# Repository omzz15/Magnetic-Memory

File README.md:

*Note: Any time I say MAD, I am refering to the memory address.

# Overview

Magnetic-core memory was an early form of non-volatile random access memory (RAM) used in early computing, notably the Apollo Guidance Computers. I am working with a friend to create our own magnetic core memory to interface with an 8-bit computer. This repository contains the code, schematics, and PCBs we make. Currently, we have made the schematic and PCB for the logic component of the memory as well as code to emulate the rest of the memory and interface with computers through serial. This is still a work in progress and has a long way to go but I thought I would share what I have.

TODO write updated docs

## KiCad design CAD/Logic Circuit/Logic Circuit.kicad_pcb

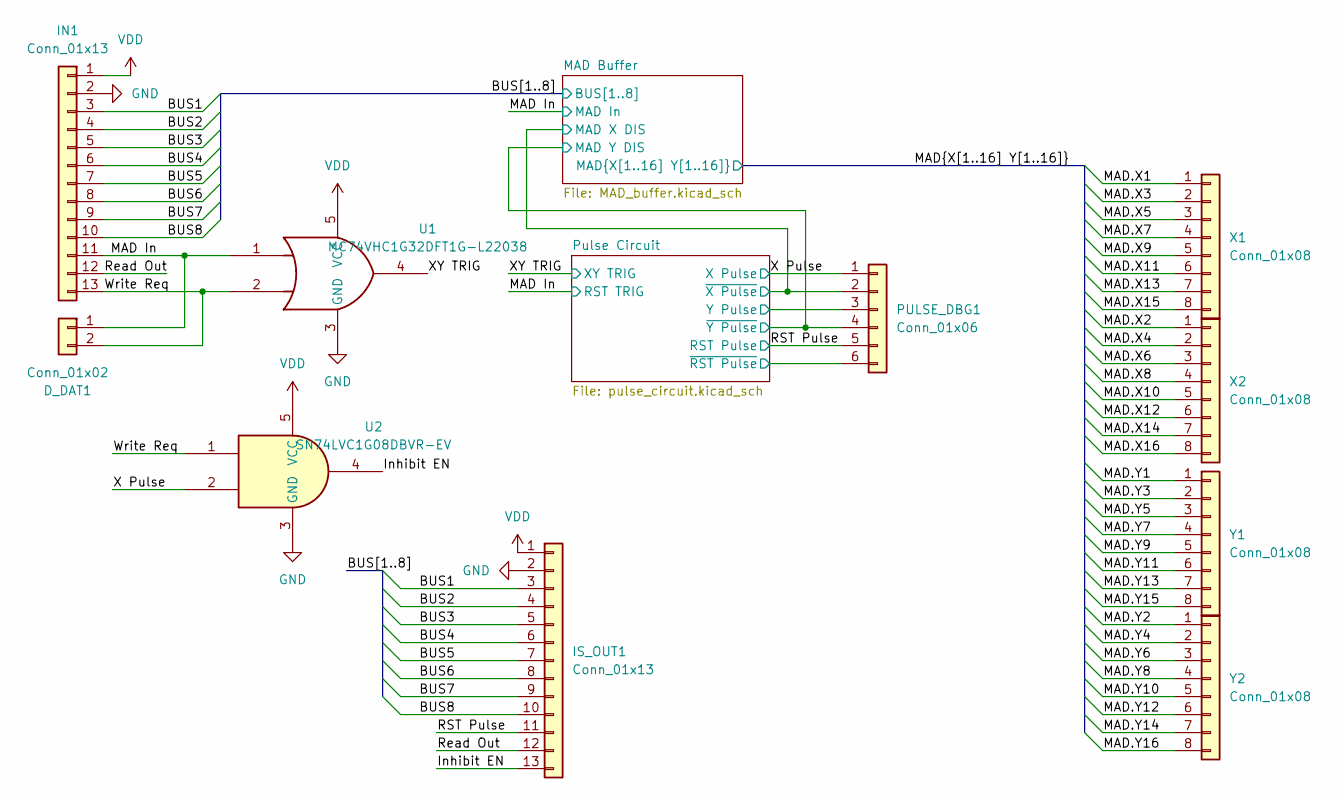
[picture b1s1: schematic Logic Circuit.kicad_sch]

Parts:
D_DAT1: Conn_01x02; PinSocket_1x02_P2.54mm_Vertical
IN1: Conn_01x13; PinHeader_1x13_P2.54mm_Vertical
IS_OUT1: Conn_01x13; PinHeader_1x13_P2.54mm_Vertical
PULSE_DBG1: Conn_01x06; PinSocket_1x06_P2.54mm_Vertical
U1: MC74VHC1G32DFT1G-L22038; SOT-353_SC-70-5_Handsoldering
U2: SN74LVC1G08DBVR-EV; SOT-23-5_HandSoldering
X1, X2: Conn_01x08; PinHeader_1x08_P2.54mm_Vertical
Y1, Y2: Conn_01x08; PinHeader_1x08_P2.54mm_Vertical

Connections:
/BUS1: IN1.3, IS_OUT1.3; also elsewhere on the board
/BUS2: IN1.4, IS_OUT1.4; also elsewhere on the board
/BUS3: IN1.5, IS_OUT1.5; also elsewhere on the board
/BUS4: IN1.6, IS_OUT1.6; also elsewhere on the board
/BUS5: IN1.7, IS_OUT1.7; also elsewhere on the board
/BUS6: IN1.8, IS_OUT1.8; also elsewhere on the board
/BUS7: IN1.9, IS_OUT1.9; also elsewhere on the board
/BUS8: IN1.10, IS_OUT1.10; also elsewhere on the board
/Inhibit EN: IS_OUT1.13, U2.4
/MAD Buffer/MAD X DIS: PULSE_DBG1.2; also elsewhere on the board
/MAD Buffer/MAD Y DIS: PULSE_DBG1.4; also elsewhere on the board
/MAD In: D_DAT1.1, IN1.11, U1.1; also elsewhere on the board
/MAD.X1: X1.1; also elsewhere on the board
/MAD.X2: X2.1; also elsewhere on the board
/MAD.X3: X1.2; also elsewhere on the board
/MAD.X4: X2.2; also elsewhere on the board
/MAD.X5: X1.3; also elsewhere on the board
/MAD.X6: X2.3; also elsewhere on the board
/MAD.X7: X1.4; also elsewhere on the board
/MAD.X8: X2.4; also elsewhere on the board
/MAD.X9: X1.5; also elsewhere on the board
/MAD.X10: X2.5; also elsewhere on the board
/MAD.X11: X1.6; also elsewhere on the board
/MAD.X12: X2.6; also elsewhere on the board
/MAD.X13: X1.7; also elsewhere on the board
/MAD.X14: X2.7; also elsewhere on the board
/MAD.X15: X1.8; also elsewhere on the board
/MAD.X16: X2.8; also elsewhere on the board
/MAD.Y1: Y1.1; also elsewhere on the board
/MAD.Y2: Y2.1; also elsewhere on the board
/MAD.Y3: Y1.2; also elsewhere on the board
/MAD.Y4: Y2.2; also elsewhere on the board
/MAD.Y5: Y1.3; also elsewhere on the board
/MAD.Y6: Y2.3; also elsewhere on the board
/MAD.Y7: Y1.4; also elsewhere on the board
/MAD.Y8: Y2.4; also elsewhere on the board
/MAD.Y9: Y1.5; also elsewhere on the board
/MAD.Y10: Y2.5; also elsewhere on the board
/MAD.Y11: Y1.6; also elsewhere on the board
/MAD.Y12: Y2.6; also elsewhere on the board
/MAD.Y13: Y1.7; also elsewhere on the board
/MAD.Y14: Y2.7; also elsewhere on the board
/MAD.Y15: Y1.8; also elsewhere on the board
/MAD.Y16: Y2.8; also elsewhere on the board
/Pulse Circuit/Y Pulse: PULSE_DBG1.3; also elsewhere on the board
/Pulse Circuit/~RST Pulse: PULSE_DBG1.6; also elsewhere on the board
/RST Pulse: IS_OUT1.11, PULSE_DBG1.5; also elsewhere on the board
/Read Out: IN1.12, IS_OUT1.12
/Write Req: D_DAT1.2, IN1.13, U1.2, U2.1
/X Pulse: PULSE_DBG1.1, U2.2; also elsewhere on the board
/XY TRIG: U1.4; also elsewhere on the board
GND: IN1.2, IS_OUT1.2, U1.3 (GND), U2.3 (GND); also elsewhere on the board
VDD: IN1.1, IS_OUT1.1, U1.5 (VCC), U2.5 (VCC); also elsewhere on the board

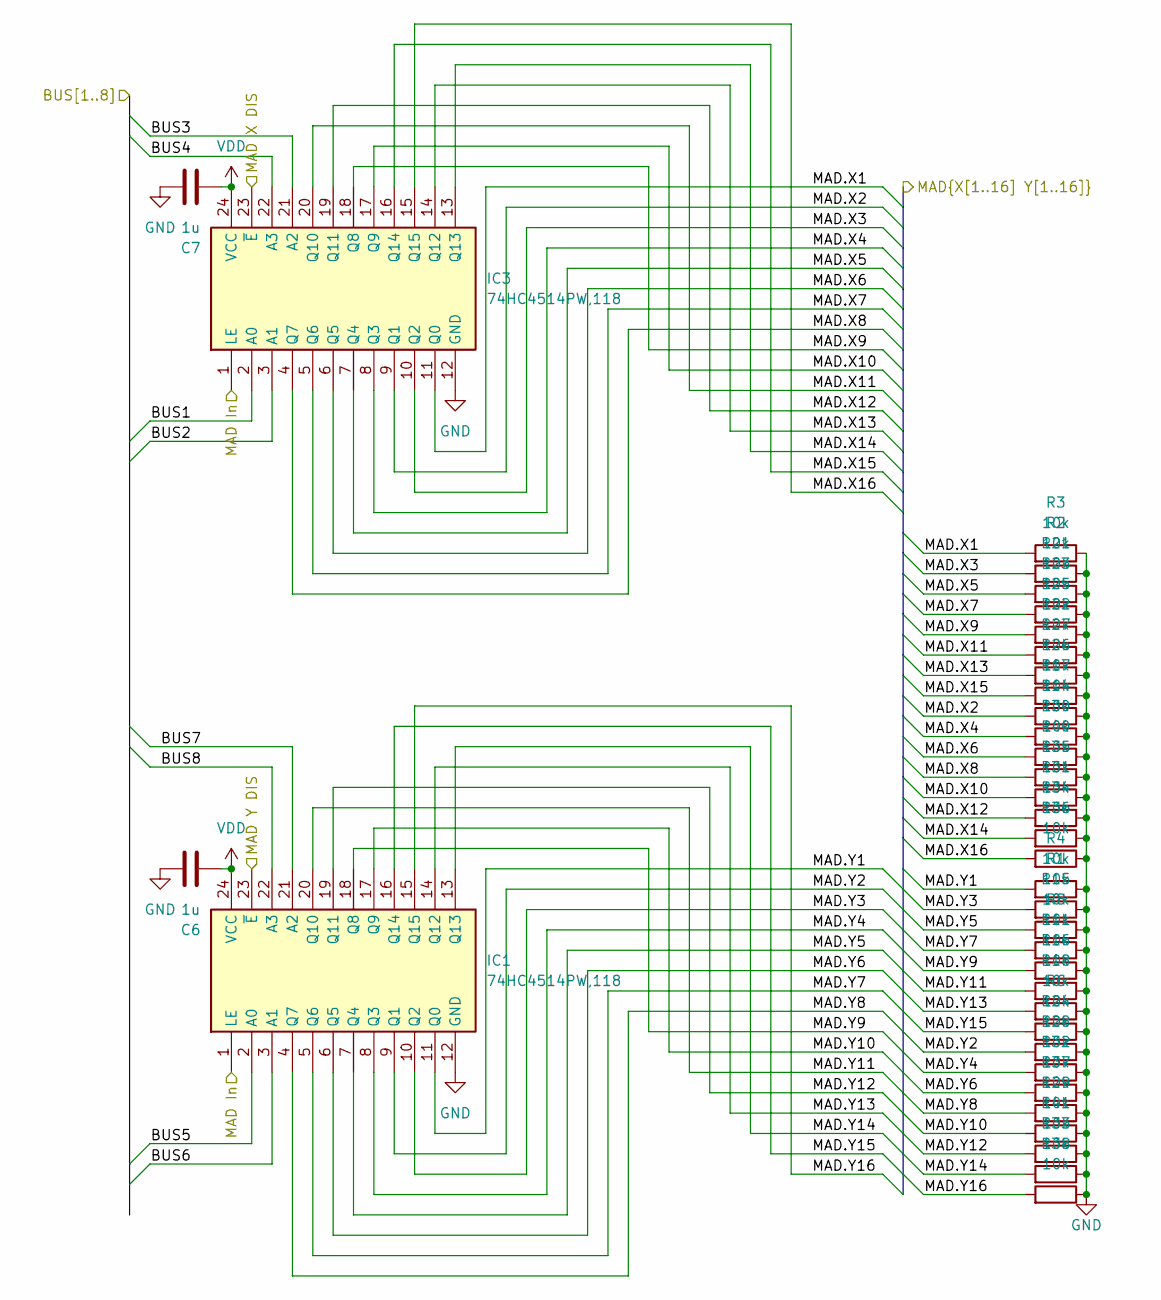
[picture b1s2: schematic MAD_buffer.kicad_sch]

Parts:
C6, C7: 1u; C_0603_1608Metric_Pad1.08x0.95mm_HandSolder
IC1, IC3: 74HC4514PW,118; SOP65P640X110-24N; Mouser Part Number 771-HC4514PW118
R1, R2, R3, R4, R6, R8, R11, R14, R15, R16, R17, R18, R21, R22, R23, R24, R25, R26, R27, R28, R29, R30, R31, R32, R33, R34, R35, R36, R37, R38, R40, R41: 10k; R_0603_1608Metric_Pad0.98x0.95mm_HandSolder

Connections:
/BUS1: IC3.2 (A0); also elsewhere on the board
/BUS2: IC3.3 (A1); also elsewhere on the board
/BUS3: IC3.21 (A2); also elsewhere on the board
/BUS4: IC3.22 (A3); also elsewhere on the board
/BUS5: IC1.2 (A0); also elsewhere on the board
/BUS6: IC1.3 (A1); also elsewhere on the board
/BUS7: IC1.21 (A2); also elsewhere on the board
/BUS8: IC1.22 (A3); also elsewhere on the board
/MAD Buffer/MAD X DIS: IC3.23 (~E); also elsewhere on the board
/MAD Buffer/MAD Y DIS: IC1.23 (~E); also elsewhere on the board
/MAD In: IC1.1 (LE), IC3.1 (LE); also elsewhere on the board
/MAD.X1: IC3.11 (Q0), R3.2; also elsewhere on the board
/MAD.X2: IC3.9 (Q1), R17.2; also elsewhere on the board
/MAD.X3: IC3.10 (Q2), R2.2; also elsewhere on the board
/MAD.X4: IC3.8 (Q3), R14.2; also elsewhere on the board
/MAD.X5: IC3.7 (Q4), R21.2; also elsewhere on the board
/MAD.X6: IC3.6 (Q5), R30.2; also elsewhere on the board
/MAD.X7: IC3.5 (Q6), R23.2; also elsewhere on the board
/MAD.X8: IC3.4 (Q7), R40.2; also elsewhere on the board
/MAD.X9: IC3.18 (Q8), R25.2; also elsewhere on the board
/MAD.X10: IC3.17 (Q9), R35.2; also elsewhere on the board
/MAD.X11: IC3.20 (Q10), R22.2; also elsewhere on the board
/MAD.X12: IC3.19 (Q11), R31.2; also elsewhere on the board
/MAD.X13: IC3.14 (Q12), R27.2; also elsewhere on the board
/MAD.X14: IC3.13 (Q13), R34.2; also elsewhere on the board
/MAD.X15: IC3.16 (Q14), R26.2; also elsewhere on the board
/MAD.X16: IC3.15 (Q15), R36.2; also elsewhere on the board
/MAD.Y1: IC1.11 (Q0), R4.2; also elsewhere on the board
/MAD.Y2: IC1.9 (Q1), R24.2; also elsewhere on the board
/MAD.Y3: IC1.10 (Q2), R1.2; also elsewhere on the board
/MAD.Y4: IC1.8 (Q3), R28.2; also elsewhere on the board
/MAD.Y5: IC1.7 (Q4), R15.2; also elsewhere on the board
/MAD.Y6: IC1.6 (Q5), R32.2; also elsewhere on the board
/MAD.Y7: IC1.5 (Q6), R8.2; also elsewhere on the board
/MAD.Y8: IC1.4 (Q7), R37.2; also elsewhere on the board
/MAD.Y9: IC1.18 (Q8), R11.2; also elsewhere on the board
/MAD.Y10: IC1.17 (Q9), R29.2; also elsewhere on the board
/MAD.Y11: IC1.20 (Q10), R16.2; also elsewhere on the board
/MAD.Y12: IC1.19 (Q11), R41.2; also elsewhere on the board
/MAD.Y13: IC1.14 (Q12), R18.2; also elsewhere on the board
/MAD.Y14: IC1.13 (Q13), R33.2; also elsewhere on the board
/MAD.Y15: IC1.16 (Q14), R6.2; also elsewhere on the board
/MAD.Y16: IC1.15 (Q15), R38.2; also elsewhere on the board
GND: C6.1, C7.1, IC1.12 (GND), IC3.12 (GND), R1.1, R2.1, R3.1, R4.1, R6.1, R8.1, R11.1, R14.1, R15.1, R16.1, R17.1, R18.1, R21.1, R22.1, R23.1, R24.1, R25.1, R26.1, R27.1, R28.1, R29.1, R30.1, R31.1, R32.1, R33.1, R34.1, R35.1, R36.1, R37.1, R38.1, R40.1, R41.1; also elsewhere on the board
VDD: C6.2, C7.2, IC1.24 (VCC), IC3.24 (VCC); also elsewhere on the board

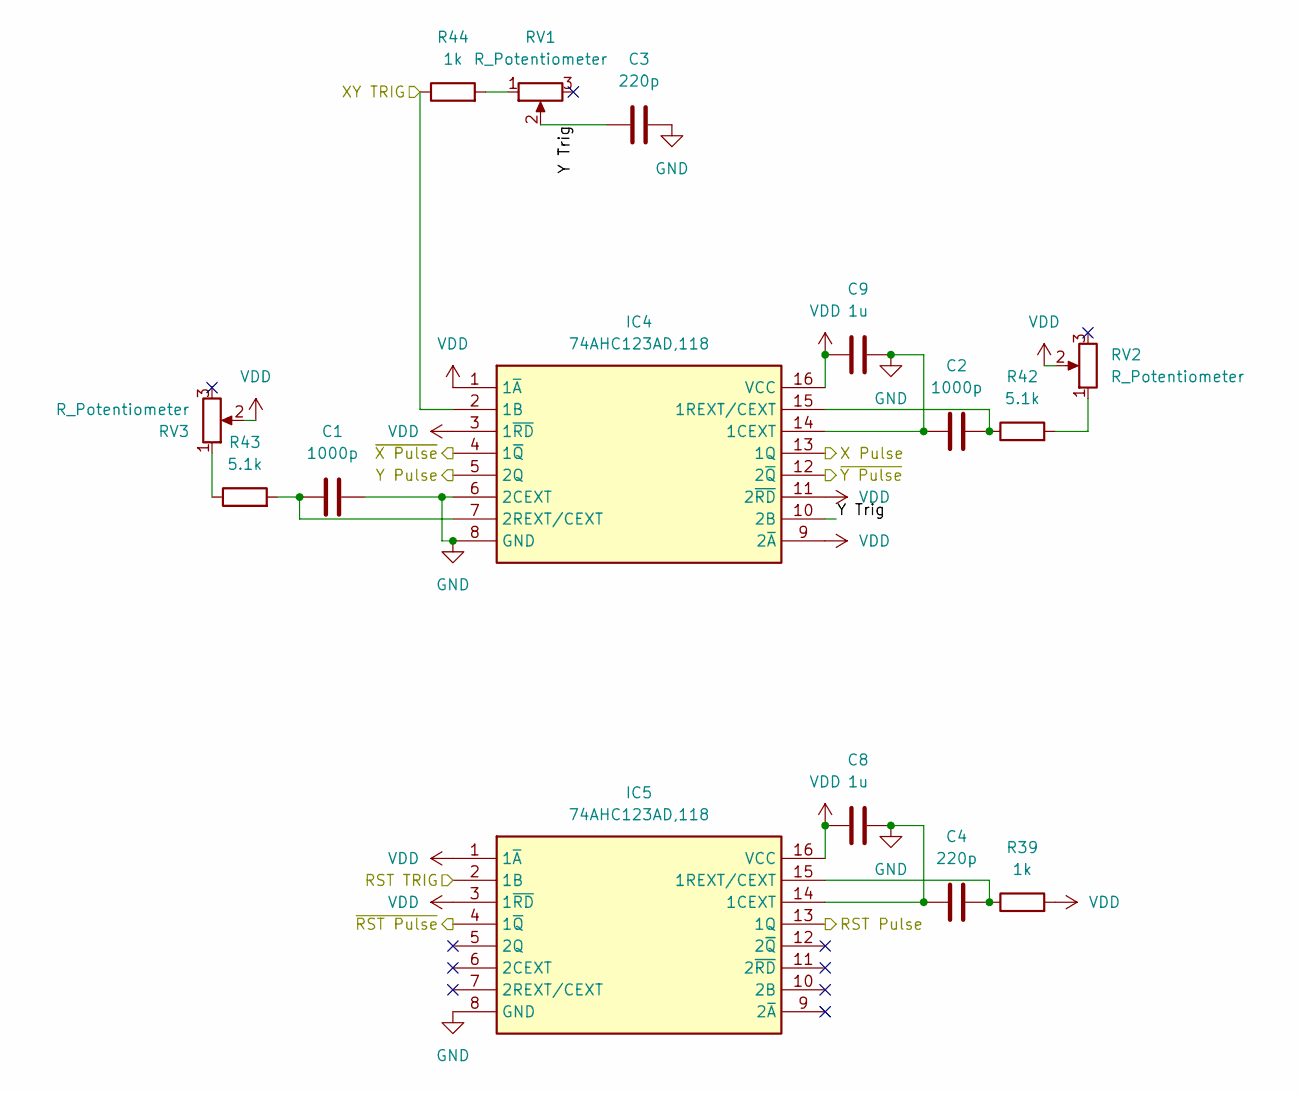
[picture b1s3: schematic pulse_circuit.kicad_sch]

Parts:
C1, C2: 1000p; C_0603_1608Metric_Pad1.08x0.95mm_HandSolder
C3, C4: 220p; C_0603_1608Metric_Pad1.08x0.95mm_HandSolder
C8, C9: 1u; C_0603_1608Metric_Pad1.08x0.95mm_HandSolder
IC4, IC5: 74AHC123AD,118; SOIC127P600X175-16N; Mouser Part Number 771-AHC123AD118
R39, R44: 1k; R_0603_1608Metric_Pad0.98x0.95mm_HandSolder
R42, R43: 5.1k; R_0603_1608Metric_Pad0.98x0.95mm_HandSolder
RV1, RV2, RV3: R_Potentiometer; Potentiometer_Bourns_3296W_Vertical

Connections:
/MAD Buffer/MAD X DIS: IC4.4 (1~Q); also elsewhere on the board
/MAD Buffer/MAD Y DIS: IC4.12 (2~Q); also elsewhere on the board
/MAD In: IC5.2 (1B); also elsewhere on the board
/Pulse Circuit/Y Pulse: IC4.5 (2Q); also elsewhere on the board
/Pulse Circuit/Y Trig: C3.1, IC4.10 (2B), RV1.2
/Pulse Circuit/~RST Pulse: IC5.4 (1~Q); also elsewhere on the board
/RST Pulse: IC5.13 (1Q); also elsewhere on the board
/X Pulse: IC4.13 (1Q); also elsewhere on the board
/XY TRIG: IC4.2 (1B), R44.1; also elsewhere on the board
GND: C1.2, C2.1, C3.2, C4.1, C8.1, C9.1, IC4.6 (2CEXT), IC4.8 (GND), IC4.14 (1CEXT), IC5.8 (GND), IC5.14 (1CEXT); also elsewhere on the board
unnamed: C2.2, IC4.15 (1REXT/CEXT), R42.1
unnamed: C1.1, IC4.7 (2REXT/CEXT), R43.2
unnamed: C4.2, IC5.15 (1REXT/CEXT), R39.1
unnamed: R42.2, RV2.1
unnamed: R43.1, RV3.1
unnamed: R44.2, RV1.1
VDD: C8.2, C9.2, IC4.1 (1~A), IC4.3 (1~RD), IC4.9 (2~A), IC4.11 (2~RD), IC4.16 (VCC), IC5.1 (1~A), IC5.3 (1~RD), IC5.16 (VCC), R39.2, RV2.2, RV3.2; also elsewhere on the board

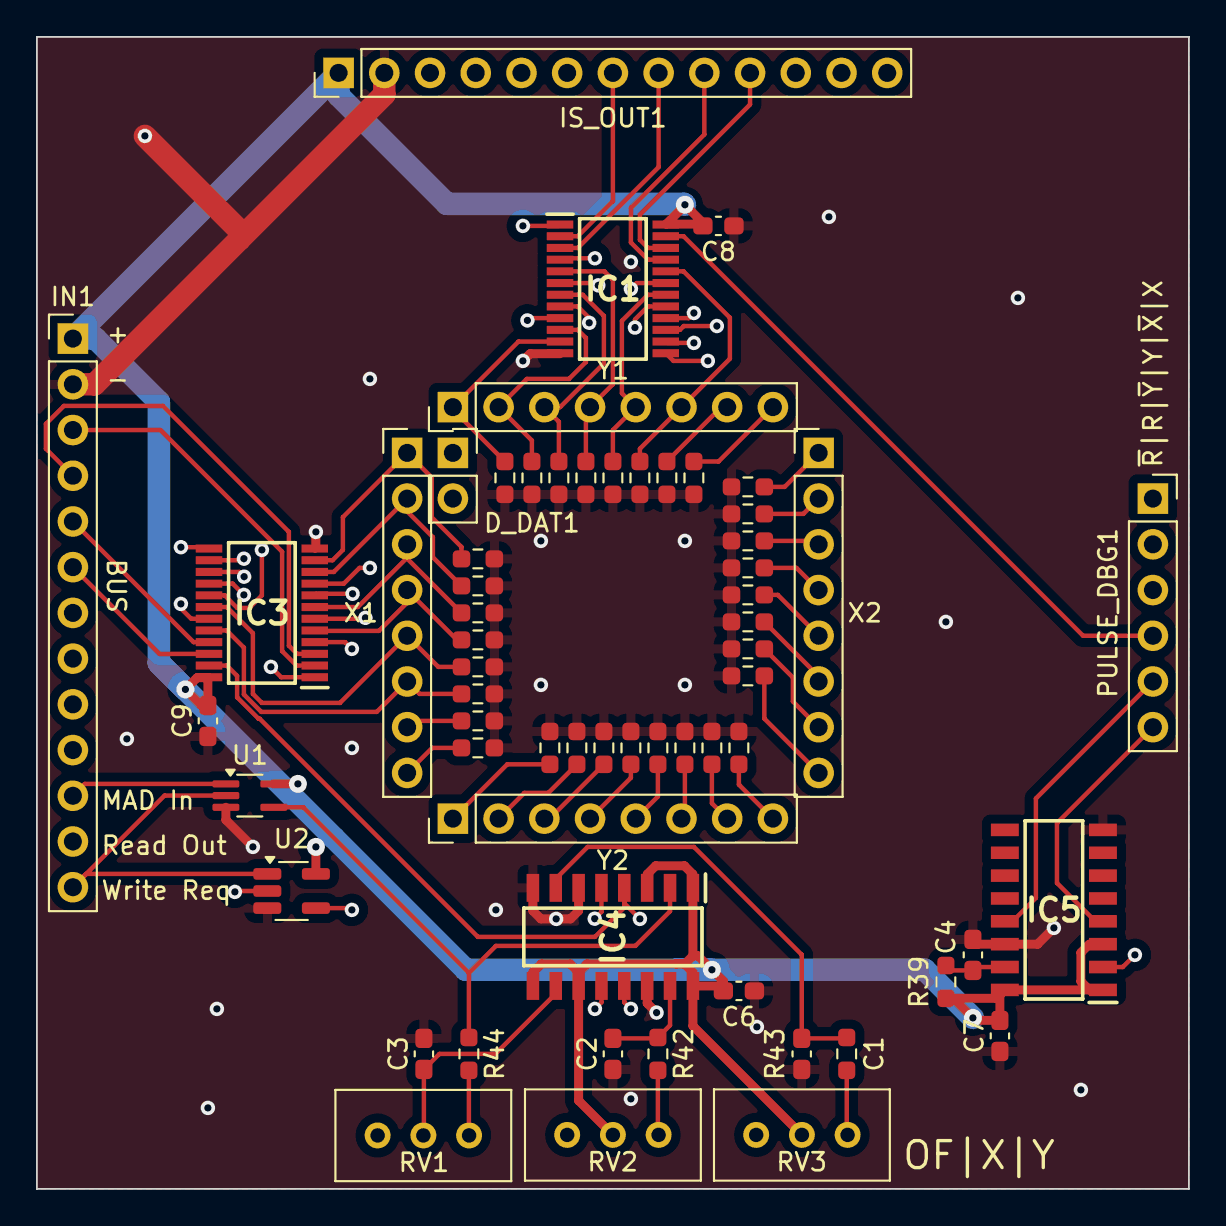
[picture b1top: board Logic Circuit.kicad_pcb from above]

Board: 4 copper layers, 64.0 x 64.0 mm, 61 parts (0 on the bottom side), 60 nets.

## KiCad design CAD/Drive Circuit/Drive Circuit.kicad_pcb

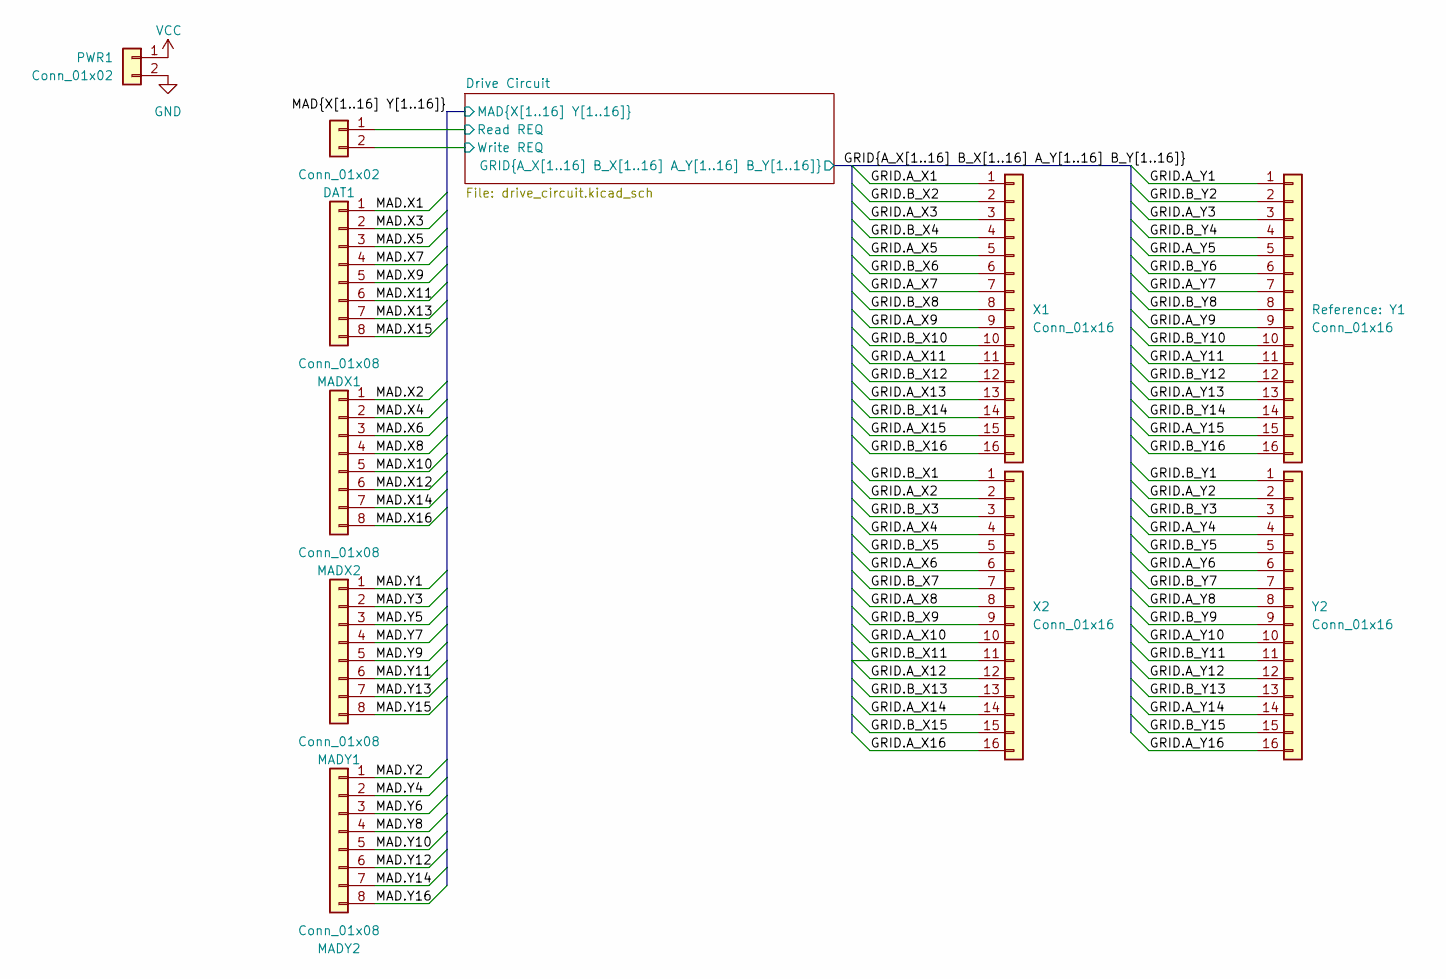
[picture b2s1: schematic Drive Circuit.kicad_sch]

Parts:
DAT1: Conn_01x02; PinHeader_1x02_P2.54mm_Vertical
MADX1, MADX2: Conn_01x08; PinHeader_1x08_P2.54mm_Vertical
MADY1, MADY2: Conn_01x08; PinHeader_1x08_P2.54mm_Vertical
PWR1: Conn_01x02; PinHeader_1x02_P2.54mm_Vertical
X1, X2: Conn_01x16; PinHeader_1x16_P2.54mm_Vertical
Y1, Y2: Conn_01x16; PinHeader_1x16_P2.54mm_Vertical

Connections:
/Drive Circuit/Read REQ: DAT1.1; also elsewhere on the board
/Drive Circuit/Write REQ: DAT1.2; also elsewhere on the board
/GRID.A_X1: X1.1; also elsewhere on the board
/GRID.A_X2: X2.2; also elsewhere on the board
/GRID.A_X3: X1.3; also elsewhere on the board
/GRID.A_X4: X2.4; also elsewhere on the board
/GRID.A_X5: X1.5; also elsewhere on the board
/GRID.A_X6: X2.6; also elsewhere on the board
/GRID.A_X7: X1.7; also elsewhere on the board
/GRID.A_X8: X2.8; also elsewhere on the board
/GRID.A_X9: X1.9; also elsewhere on the board
/GRID.A_X10: X2.10; also elsewhere on the board
/GRID.A_X11: X1.11; also elsewhere on the board
/GRID.A_X12: X2.12; also elsewhere on the board
/GRID.A_X13: X1.13; also elsewhere on the board
/GRID.A_X14: X2.14; also elsewhere on the board
/GRID.A_X15: X1.15; also elsewhere on the board
/GRID.A_X16: X2.16; also elsewhere on the board
/GRID.A_Y1: Y1.1; also elsewhere on the board
/GRID.A_Y2: Y2.2; also elsewhere on the board
/GRID.A_Y3: Y1.3; also elsewhere on the board
/GRID.A_Y4: Y2.4; also elsewhere on the board
/GRID.A_Y5: Y1.5; also elsewhere on the board
/GRID.A_Y6: Y2.6; also elsewhere on the board
/GRID.A_Y7: Y1.7; also elsewhere on the board
/GRID.A_Y8: Y2.8; also elsewhere on the board
/GRID.A_Y9: Y1.9; also elsewhere on the board
/GRID.A_Y10: Y2.10; also elsewhere on the board
/GRID.A_Y11: Y1.11; also elsewhere on the board
/GRID.A_Y12: Y2.12; also elsewhere on the board
/GRID.A_Y13: Y1.13; also elsewhere on the board
/GRID.A_Y14: Y2.14; also elsewhere on the board
/GRID.A_Y15: Y1.15; also elsewhere on the board
/GRID.A_Y16: Y2.16; also elsewhere on the board
/GRID.B_X1: X2.1; also elsewhere on the board
/GRID.B_X2: X1.2; also elsewhere on the board
/GRID.B_X3: X2.3; also elsewhere on the board
/GRID.B_X4: X1.4; also elsewhere on the board
/GRID.B_X5: X2.5; also elsewhere on the board
/GRID.B_X6: X1.6; also elsewhere on the board
/GRID.B_X7: X2.7; also elsewhere on the board
/GRID.B_X8: X1.8; also elsewhere on the board
/GRID.B_X9: X2.9; also elsewhere on the board
/GRID.B_X10: X1.10; also elsewhere on the board
/GRID.B_X11: X2.11; also elsewhere on the board
/GRID.B_X12: X1.12; also elsewhere on the board
/GRID.B_X13: X2.13; also elsewhere on the board
/GRID.B_X14: X1.14; also elsewhere on the board
/GRID.B_X15: X2.15; also elsewhere on the board
/GRID.B_X16: X1.16; also elsewhere on the board
/GRID.B_Y1: Y2.1; also elsewhere on the board
/GRID.B_Y2: Y1.2; also elsewhere on the board
/GRID.B_Y3: Y2.3; also elsewhere on the board
/GRID.B_Y4: Y1.4; also elsewhere on the board
/GRID.B_Y5: Y2.5; also elsewhere on the board
/GRID.B_Y6: Y1.6; also elsewhere on the board
/GRID.B_Y7: Y2.7; also elsewhere on the board
/GRID.B_Y8: Y1.8; also elsewhere on the board
/GRID.B_Y9: Y2.9; also elsewhere on the board
/GRID.B_Y10: Y1.10; also elsewhere on the board
/GRID.B_Y11: Y2.11; also elsewhere on the board
/GRID.B_Y12: Y1.12; also elsewhere on the board
/GRID.B_Y13: Y2.13; also elsewhere on the board
/GRID.B_Y14: Y1.14; also elsewhere on the board
/GRID.B_Y15: Y2.15; also elsewhere on the board
/GRID.B_Y16: Y1.16; also elsewhere on the board
/MAD.X1: MADX1.1; also elsewhere on the board
/MAD.X2: MADX2.1; also elsewhere on the board
/MAD.X3: MADX1.2; also elsewhere on the board
/MAD.X4: MADX2.2; also elsewhere on the board
/MAD.X5: MADX1.3; also elsewhere on the board
/MAD.X6: MADX2.3; also elsewhere on the board
/MAD.X7: MADX1.4; also elsewhere on the board
/MAD.X8: MADX2.4; also elsewhere on the board
/MAD.X9: MADX1.5; also elsewhere on the board
/MAD.X10: MADX2.5; also elsewhere on the board
/MAD.X11: MADX1.6; also elsewhere on the board
/MAD.X12: MADX2.6; also elsewhere on the board
/MAD.X13: MADX1.7; also elsewhere on the board
/MAD.X14: MADX2.7; also elsewhere on the board
/MAD.X15: MADX1.8; also elsewhere on the board
/MAD.X16: MADX2.8; also elsewhere on the board
/MAD.Y1: MADY1.1; also elsewhere on the board
/MAD.Y2: MADY2.1; also elsewhere on the board
/MAD.Y3: MADY1.2; also elsewhere on the board
/MAD.Y4: MADY2.2; also elsewhere on the board
/MAD.Y5: MADY1.3; also elsewhere on the board
/MAD.Y6: MADY2.3; also elsewhere on the board
/MAD.Y7: MADY1.4; also elsewhere on the board
/MAD.Y8: MADY2.4; also elsewhere on the board
/MAD.Y9: MADY1.5; also elsewhere on the board
/MAD.Y10: MADY2.5; also elsewhere on the board
/MAD.Y11: MADY1.6; also elsewhere on the board
/MAD.Y12: MADY2.6; also elsewhere on the board
/MAD.Y13: MADY1.7; also elsewhere on the board
/MAD.Y14: MADY2.7; also elsewhere on the board
/MAD.Y15: MADY1.8; also elsewhere on the board
/MAD.Y16: MADY2.8; also elsewhere on the board
GND: PWR1.2; also elsewhere on the board
VCC: PWR1.1; also elsewhere on the board

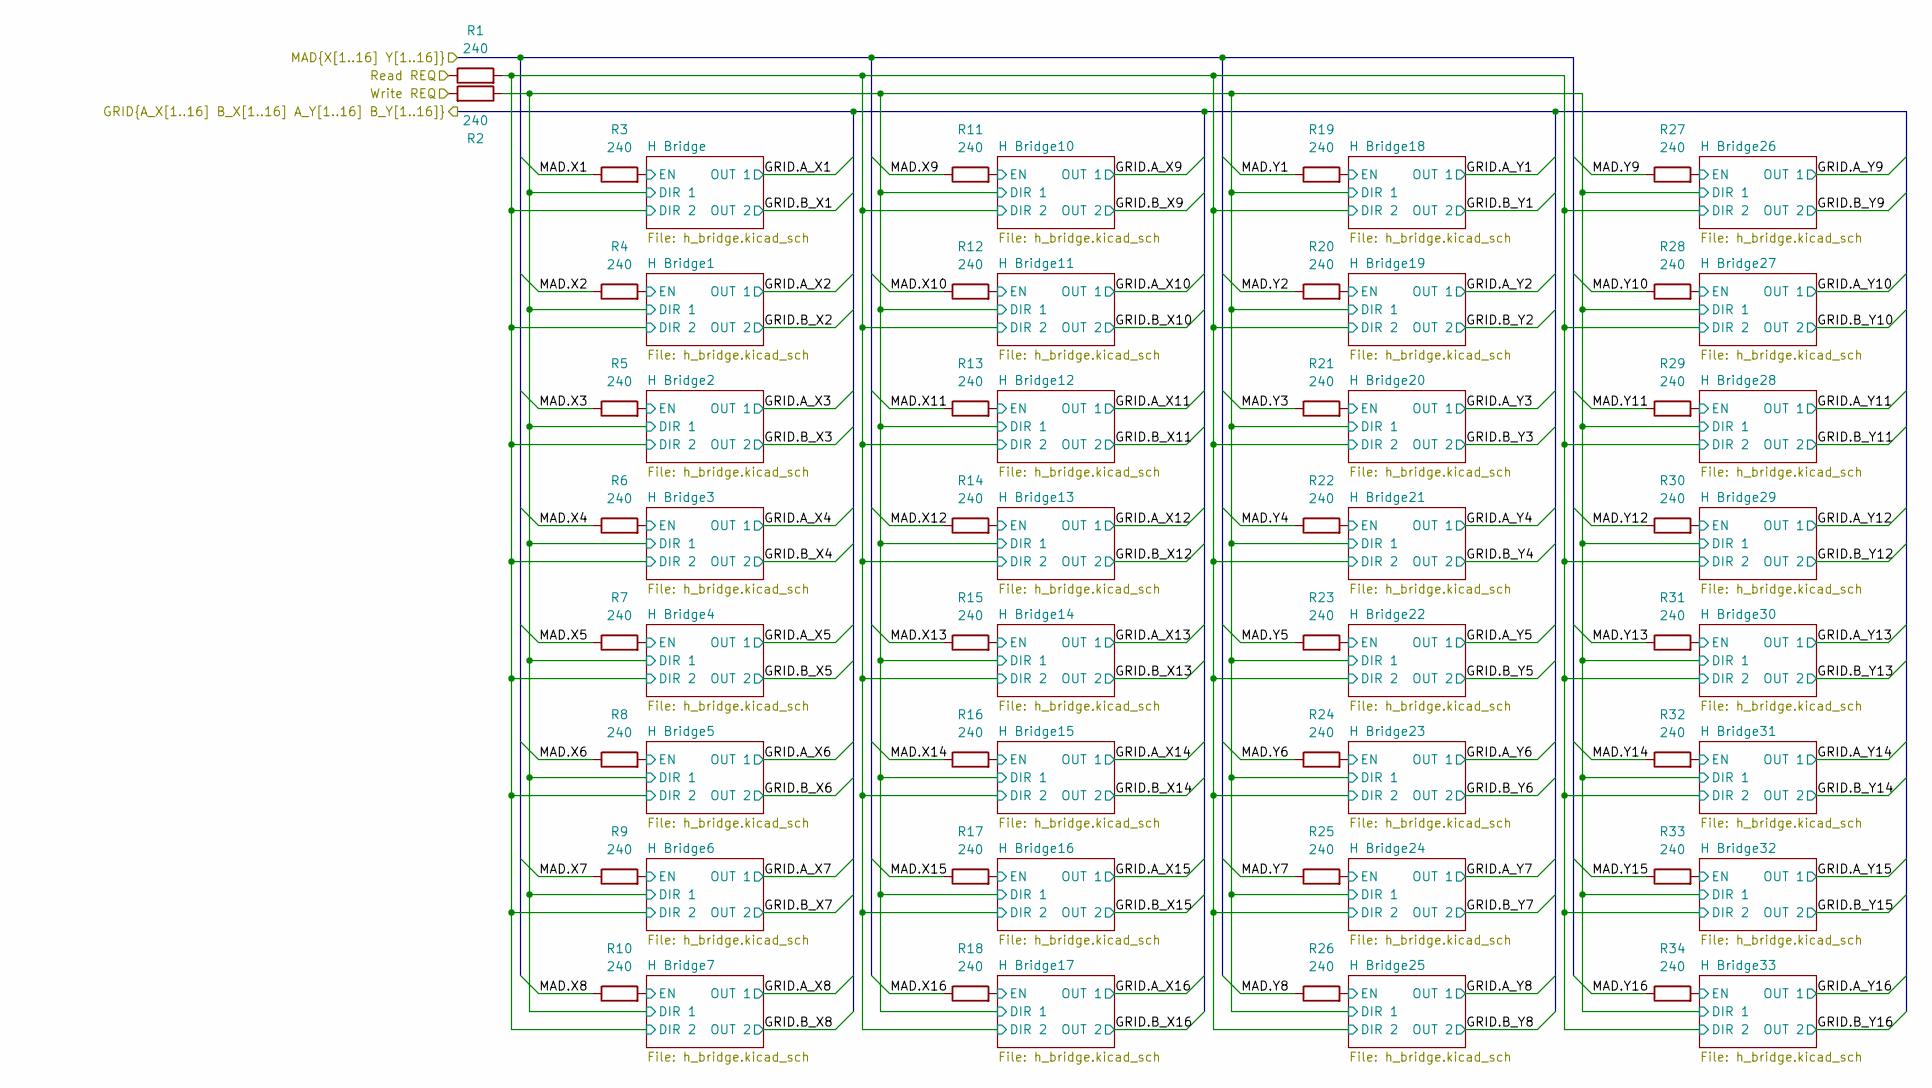
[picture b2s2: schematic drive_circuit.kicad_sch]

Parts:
R1, R2, R3, R4, R5, R6, R7, R8, R9, R10, R11, R12, R13, R14, R15, R16, R17, R18, R19, R20, R21, R22, R23, R24, R25, R26, R27, R28, R29, R30, R31, R32, R33, R34: 240; R_0603_1608Metric_Pad0.98x0.95mm_HandSolder

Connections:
/Drive Circuit/H Bridge1/EN: R4.2; also elsewhere on the board
/Drive Circuit/H Bridge2/EN: R5.2; also elsewhere on the board
/Drive Circuit/H Bridge3/EN: R6.2; also elsewhere on the board
/Drive Circuit/H Bridge4/EN: R7.2; also elsewhere on the board
/Drive Circuit/H Bridge5/EN: R8.2; also elsewhere on the board
/Drive Circuit/H Bridge6/EN: R9.2; also elsewhere on the board
/Drive Circuit/H Bridge7/EN: R10.2; also elsewhere on the board
/Drive Circuit/H Bridge10/EN: R11.2; also elsewhere on the board
/Drive Circuit/H Bridge11/EN: R12.2; also elsewhere on the board
/Drive Circuit/H Bridge12/EN: R13.2; also elsewhere on the board
/Drive Circuit/H Bridge13/EN: R14.2; also elsewhere on the board
/Drive Circuit/H Bridge14/EN: R15.2; also elsewhere on the board
/Drive Circuit/H Bridge15/EN: R16.2; also elsewhere on the board
/Drive Circuit/H Bridge16/EN: R17.2; also elsewhere on the board
/Drive Circuit/H Bridge17/EN: R18.2; also elsewhere on the board
/Drive Circuit/H Bridge18/EN: R19.2; also elsewhere on the board
/Drive Circuit/H Bridge19/EN: R20.2; also elsewhere on the board
/Drive Circuit/H Bridge20/EN: R21.2; also elsewhere on the board
/Drive Circuit/H Bridge21/EN: R22.2; also elsewhere on the board
/Drive Circuit/H Bridge22/EN: R23.2; also elsewhere on the board
/Drive Circuit/H Bridge23/EN: R24.2; also elsewhere on the board
/Drive Circuit/H Bridge24/EN: R25.2; also elsewhere on the board
/Drive Circuit/H Bridge25/EN: R26.2; also elsewhere on the board
/Drive Circuit/H Bridge26/EN: R27.2; also elsewhere on the board
/Drive Circuit/H Bridge27/EN: R28.2; also elsewhere on the board
/Drive Circuit/H Bridge28/EN: R29.2; also elsewhere on the board
/Drive Circuit/H Bridge29/EN: R30.2; also elsewhere on the board
/Drive Circuit/H Bridge30/EN: R31.2; also elsewhere on the board
/Drive Circuit/H Bridge31/EN: R32.2; also elsewhere on the board
/Drive Circuit/H Bridge32/EN: R33.2; also elsewhere on the board
/Drive Circuit/H Bridge33/EN: R34.2; also elsewhere on the board
/Drive Circuit/H Bridge/DIR 1: R2.1; also elsewhere on the board
/Drive Circuit/H Bridge/DIR 2: R1.2; also elsewhere on the board
/Drive Circuit/H Bridge/EN: R3.2; also elsewhere on the board
/Drive Circuit/Read REQ: R1.1; also elsewhere on the board
/Drive Circuit/Write REQ: R2.2; also elsewhere on the board
/MAD.X1: R3.1; also elsewhere on the board
/MAD.X2: R4.1; also elsewhere on the board
/MAD.X3: R5.1; also elsewhere on the board
/MAD.X4: R6.1; also elsewhere on the board
/MAD.X5: R7.1; also elsewhere on the board
/MAD.X6: R8.1; also elsewhere on the board
/MAD.X7: R9.1; also elsewhere on the board
/MAD.X8: R10.1; also elsewhere on the board
/MAD.X9: R11.1; also elsewhere on the board
/MAD.X10: R12.1; also elsewhere on the board
/MAD.X11: R13.1; also elsewhere on the board
/MAD.X12: R14.1; also elsewhere on the board
/MAD.X13: R15.1; also elsewhere on the board
/MAD.X14: R16.1; also elsewhere on the board
/MAD.X15: R17.1; also elsewhere on the board
/MAD.X16: R18.1; also elsewhere on the board
/MAD.Y1: R19.1; also elsewhere on the board
/MAD.Y2: R20.1; also elsewhere on the board
/MAD.Y3: R21.1; also elsewhere on the board
/MAD.Y4: R22.1; also elsewhere on the board
/MAD.Y5: R23.1; also elsewhere on the board
/MAD.Y6: R24.1; also elsewhere on the board
/MAD.Y7: R25.1; also elsewhere on the board
/MAD.Y8: R26.1; also elsewhere on the board
/MAD.Y9: R27.1; also elsewhere on the board
/MAD.Y10: R28.1; also elsewhere on the board
/MAD.Y11: R29.1; also elsewhere on the board
/MAD.Y12: R30.1; also elsewhere on the board
/MAD.Y13: R31.1; also elsewhere on the board
/MAD.Y14: R32.1; also elsewhere on the board
/MAD.Y15: R33.1; also elsewhere on the board
/MAD.Y16: R34.1; also elsewhere on the board
